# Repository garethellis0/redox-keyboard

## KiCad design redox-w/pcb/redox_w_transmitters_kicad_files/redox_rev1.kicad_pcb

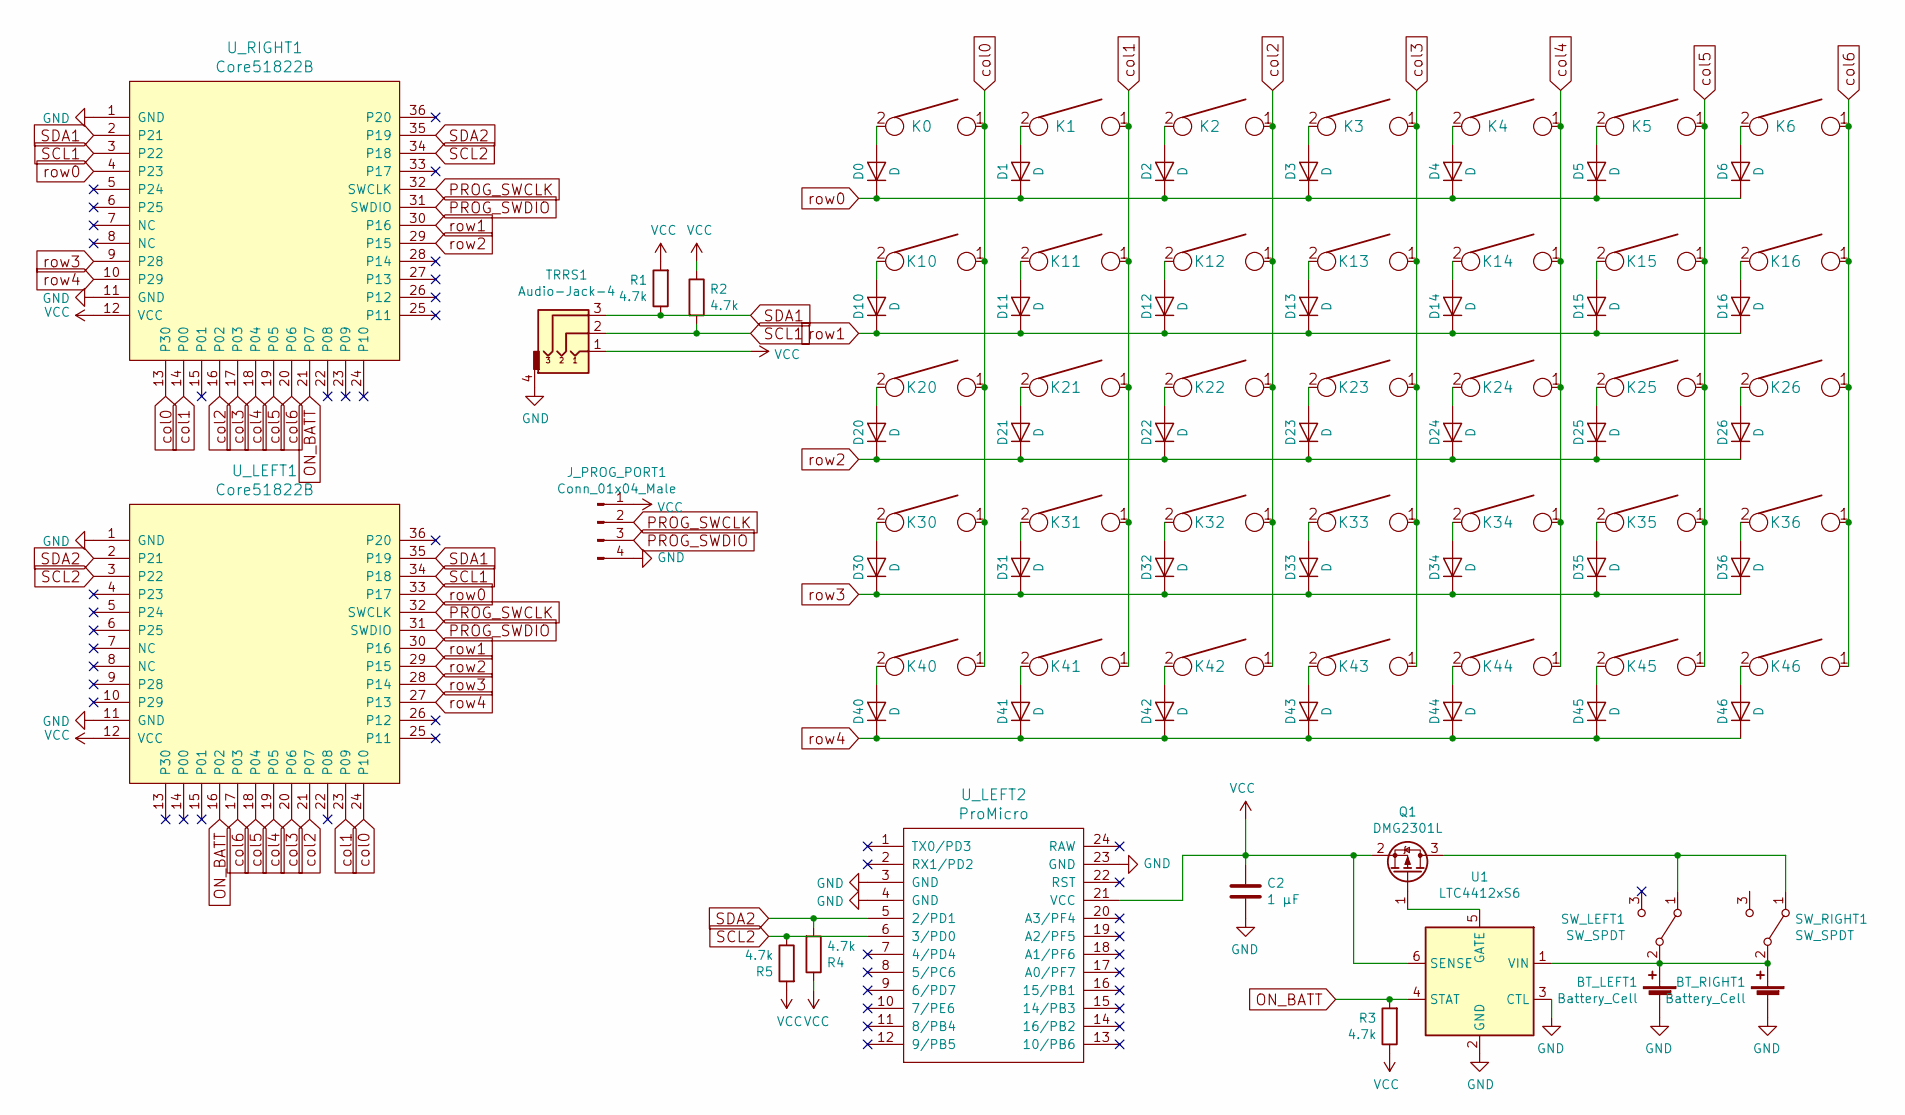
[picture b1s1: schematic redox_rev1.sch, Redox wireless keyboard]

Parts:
BT_LEFT1: Battery_Cell; BatteryHolder_Keystone_3034_1x20mm
BT_RIGHT1: Battery_Cell; BatteryHolder_Keystone_3034_1x20mm
C2: 1 μF; C_0805_2012Metric_Pad1.15x1.40mm_HandSolder
D0, D1, D2, D3, D4, D5, D6, D10, D11, D12, D13, D14, D15, D16, D20, D21, D22, D23, D24, D25, D26, D30, D31, D32, D33, D34, D35, D36, D40, D41, D42, D43, D44, D45, D46: D; Diode-dual
J_PROG_PORT1: Conn_01x04_Male; PinHeader_1x04_P2.54mm_Horizontal
K0, K10, K20, K30, K44: KEYSW; Mx_Alps_125-dualside
K1, K2, K3, K4, K5, K6, K11, K12, K13, K14, K15, K21, K22, K23, K24, K25, K26, K31, K32, K33, K34, K35, K36, K40, K41, K42, K43: KEYSW; Mx_Alps_100-dualside
K16, K45, K46: KEYSW; Mx_Alps_150-dualside
Q1: DMG2301L; SOT-23
R1, R2, R3, R4, R5: 4.7k; R_0805_2012Metric_Pad1.15x1.40mm_HandSolder
SW_LEFT1: SW_SPDT; SW_SPDT_CK-JS102011SAQN
SW_RIGHT1: SW_SPDT; SW_SPDT_CK-JS102011SAQN
TRRS1: Audio-Jack-4; TRRS-PJ-320A-dual
U1: LTC4412xS6; TSOT-23-6
U_LEFT1: Core51822B; MY-YJ-14015-Module
U_LEFT2: ProMicro; ArduinoProMicro
U_RIGHT1: Core51822B; MY-YJ-14015-Module

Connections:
GND: BT_LEFT1.2 (-), BT_RIGHT1.2 (-), C2.2, J_PROG_PORT1.4, TRRS1.4, U1.2 (GND), U1.3 (CTL), U_LEFT1.1 (GND), U_LEFT1.11 (GND), U_LEFT2.3 (GND), U_LEFT2.4 (GND), U_LEFT2.23 (GND), U_RIGHT1.1 (GND), U_RIGHT1.11 (GND)
unnamed: BT_LEFT1.1 (+), BT_RIGHT1.1 (+), SW_LEFT1.2 (B), SW_RIGHT1.2 (B), U1.1 (VIN)
unnamed: D0.2 (A), K0.2
unnamed: D1.2 (A), K1.2
unnamed: D2.2 (A), K2.2
unnamed: D3.2 (A), K3.2
unnamed: D4.2 (A), K4.2
unnamed: D5.2 (A), K5.2
unnamed: D6.2 (A), K6.2
unnamed: D10.2 (A), K10.2
unnamed: D11.2 (A), K11.2
unnamed: D12.2 (A), K12.2
unnamed: D13.2 (A), K13.2
unnamed: D14.2 (A), K14.2
unnamed: D15.2 (A), K15.2
unnamed: D16.2 (A), K16.2
unnamed: D20.2 (A), K20.2
unnamed: D21.2 (A), K21.2
unnamed: D22.2 (A), K22.2
unnamed: D23.2 (A), K23.2
unnamed: D24.2 (A), K24.2
unnamed: D25.2 (A), K25.2
unnamed: D26.2 (A), K26.2
unnamed: D30.2 (A), K30.2
unnamed: D31.2 (A), K31.2
unnamed: D32.2 (A), K32.2
unnamed: D33.2 (A), K33.2
unnamed: D34.2 (A), K34.2
unnamed: D35.2 (A), K35.2
unnamed: D36.2 (A), K36.2
unnamed: D40.2 (A), K40.2
unnamed: D41.2 (A), K41.2
unnamed: D42.2 (A), K42.2
unnamed: D43.2 (A), K43.2
unnamed: D44.2 (A), K44.2
unnamed: D45.2 (A), K45.2
unnamed: D46.2 (A), K46.2
unnamed: Q1.1 (G), U1.5 (GATE)
unnamed: Q1.3 (D), SW_LEFT1.1 (A), SW_RIGHT1.1 (A)
ON_BATT: R3.2, U1.4 (STAT), U_LEFT1.16 (P02), U_RIGHT1.21 (P07)
PROG_SWCLK: J_PROG_PORT1.2, U_LEFT1.32 (SWCLK), U_RIGHT1.32 (SWCLK)
PROG_SWDIO: J_PROG_PORT1.3, U_LEFT1.31 (SWDIO), U_RIGHT1.31 (SWDIO)
SCL1: R2.2, TRRS1.2, U_LEFT1.34 (P18), U_RIGHT1.3 (P22)
SCL2: R5.1, U_LEFT1.3 (P22), U_LEFT2.6 (3/PD0), U_RIGHT1.34 (P18)
SDA1: R1.1, TRRS1.3, U_LEFT1.35 (P19), U_RIGHT1.2 (P21)
SDA2: R4.2, U_LEFT1.2 (P21), U_LEFT2.5 (2/PD1), U_RIGHT1.35 (P19)
VCC: C2.1, J_PROG_PORT1.1, Q1.2 (S), R1.2, R2.1, R3.1, R4.1, R5.2, TRRS1.1, U1.6 (SENSE), U_LEFT1.12 (VCC), U_LEFT2.21 (VCC), U_RIGHT1.12 (VCC)
col0: K0.1, K10.1, K20.1, K30.1, K40.1, U_LEFT1.24 (P10), U_RIGHT1.13 (P30)
col1: K1.1, K11.1, K21.1, K31.1, K41.1, U_LEFT1.23 (P09), U_RIGHT1.14 (P00)
col2: K2.1, K12.1, K22.1, K32.1, K42.1, U_LEFT1.21 (P07), U_RIGHT1.16 (P02)
col3: K3.1, K13.1, K23.1, K33.1, K43.1, U_LEFT1.20 (P06), U_RIGHT1.17 (P03)
col4: K4.1, K14.1, K24.1, K34.1, K44.1, U_LEFT1.19 (P05), U_RIGHT1.18 (P04)
col5: K5.1, K15.1, K25.1, K35.1, K45.1, U_LEFT1.18 (P04), U_RIGHT1.19 (P05)
col6: K6.1, K16.1, K26.1, K36.1, K46.1, U_LEFT1.17 (P03), U_RIGHT1.20 (P06)
row0: D0.1 (K), D1.1 (K), D2.1 (K), D3.1 (K), D4.1 (K), D5.1 (K), D6.1 (K), U_LEFT1.33 (P17), U_RIGHT1.4 (P23)
row1: D10.1 (K), D11.1 (K), D12.1 (K), D13.1 (K), D14.1 (K), D15.1 (K), D16.1 (K), U_LEFT1.30 (P16), U_RIGHT1.30 (P16)
row2: D20.1 (K), D21.1 (K), D22.1 (K), D23.1 (K), D24.1 (K), D25.1 (K), D26.1 (K), U_LEFT1.29 (P15), U_RIGHT1.29 (P15)
row3: D30.1 (K), D31.1 (K), D32.1 (K), D33.1 (K), D34.1 (K), D35.1 (K), D36.1 (K), U_LEFT1.28 (P14), U_RIGHT1.9 (P28)
row4: D40.1 (K), D41.1 (K), D42.1 (K), D43.1 (K), D44.1 (K), D45.1 (K), D46.1 (K), U_LEFT1.27 (P13), U_RIGHT1.10 (P29)

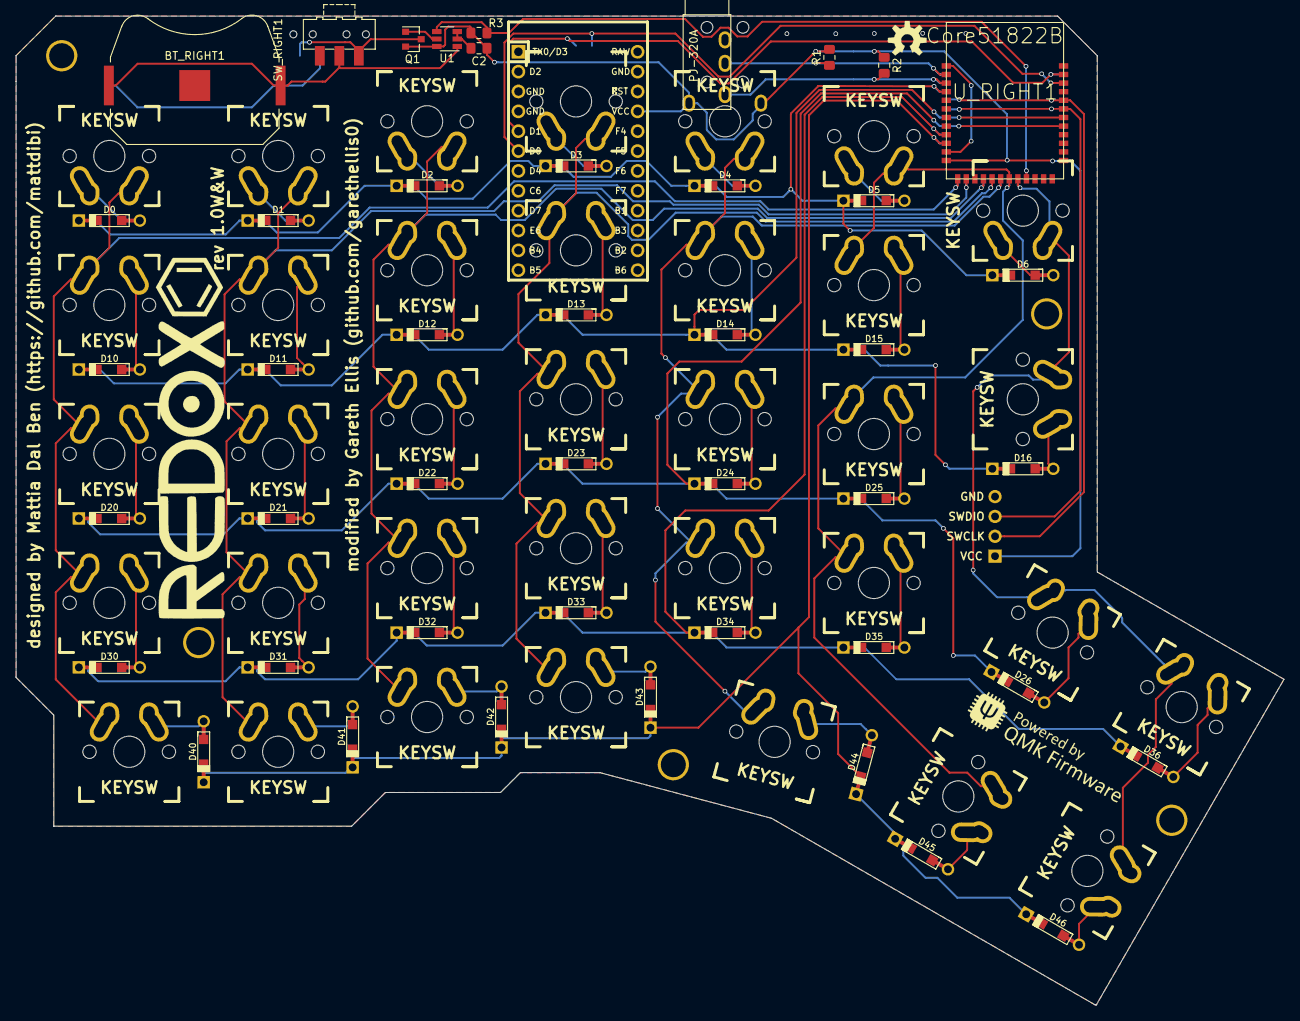
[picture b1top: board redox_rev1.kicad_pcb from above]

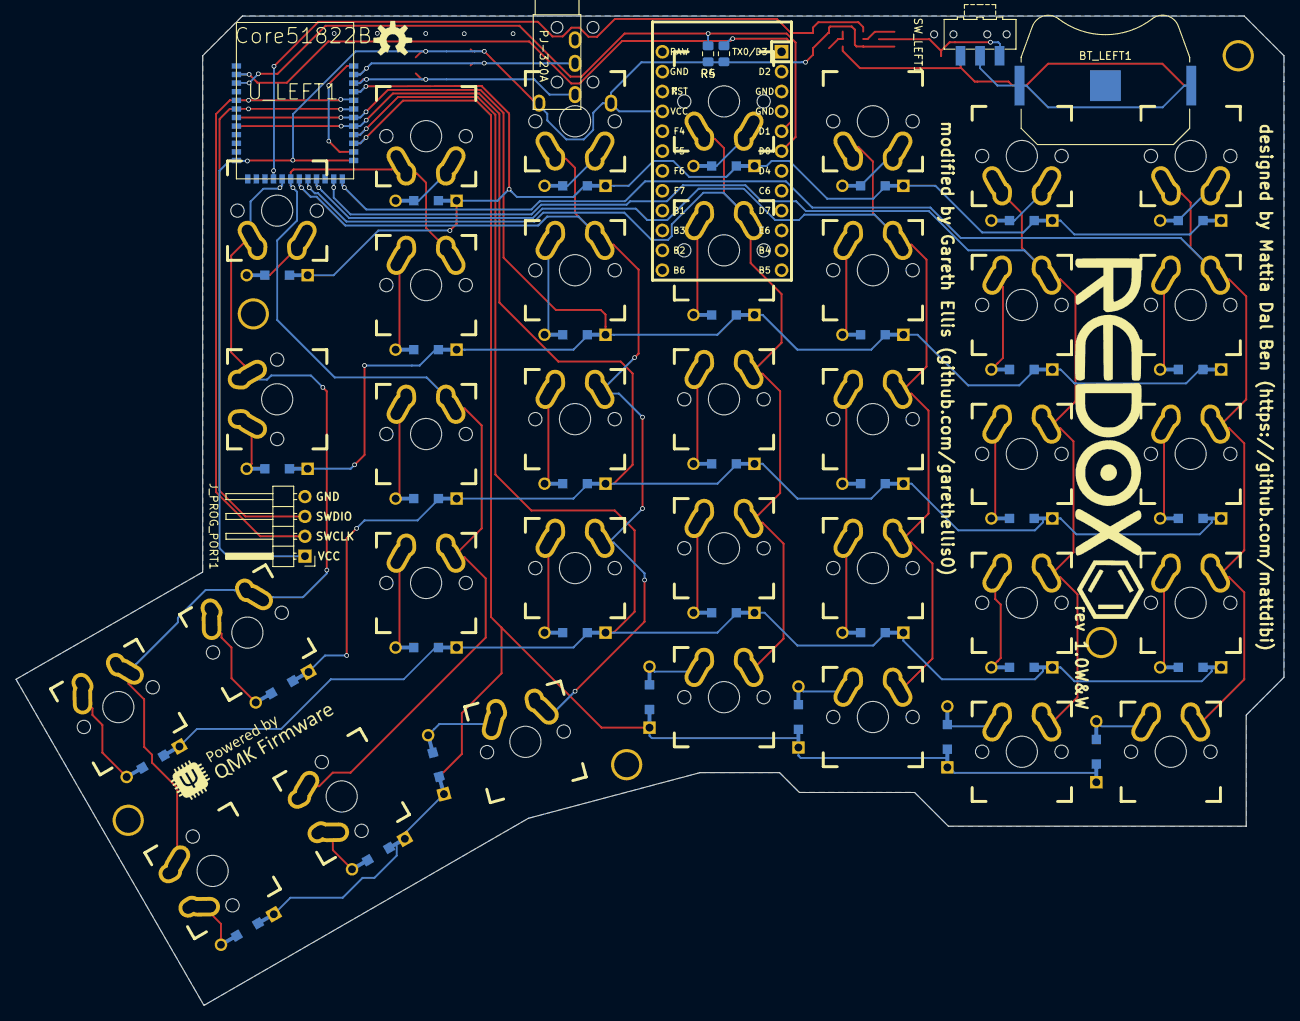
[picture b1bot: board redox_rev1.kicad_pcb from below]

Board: 2 copper layers, 162.2 x 126.5 mm, 92 parts (6 on the bottom side), 59 nets.

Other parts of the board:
HOLE_M3, HOLE_M3#2, HOLE_M3#3, HOLE_M3#4, HOLE_M3#5: VAL**; HOLE_M3

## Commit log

2020-03-28 Unzipped kicad files and initial schematic updates
2020-03-30 Misc. Folder Restructure
2020-03-30 WIP - Right Before PCB Update
2020-03-31 Right After Schematic Import to PCB - Fill Removed
2020-03-31 Moved Switch Closer To Battery On PCB
2020-03-31 Arduino ProMicro In Place On PCB, Finished Re-Routing Around It
2020-04-01 Finished Placing Power Circuitry On PCB
2020-04-01 Moved Power Circuitry To Make Room For Serial Lines From YJ To ProMicro
2020-04-01 Moved Row Wiring On YJ To New Configuration
2020-04-01 Renamed (Incorrectly) Named VCC0 Label To VCC1 And Rerouted Columns To Make Space For Headphone Jack
2020-04-01 Imported Fixed Label From Previous Commit Into PCB
2020-04-01 Emplaced Jumpers On PCB
2020-04-01 Roughly Finished PCB - Changed To Not Mirror Power Circuit
2020-04-01 OK, NOW we're roughly done
2020-04-02 PCB Roughly Finished - All Labels In Place
2020-04-02 Tweaking After Checking JLcPCB Submission
2020-04-02 More Logo Tweaking
2020-05-20 Fixed Bug Where row1 and row2 Were on NC's
